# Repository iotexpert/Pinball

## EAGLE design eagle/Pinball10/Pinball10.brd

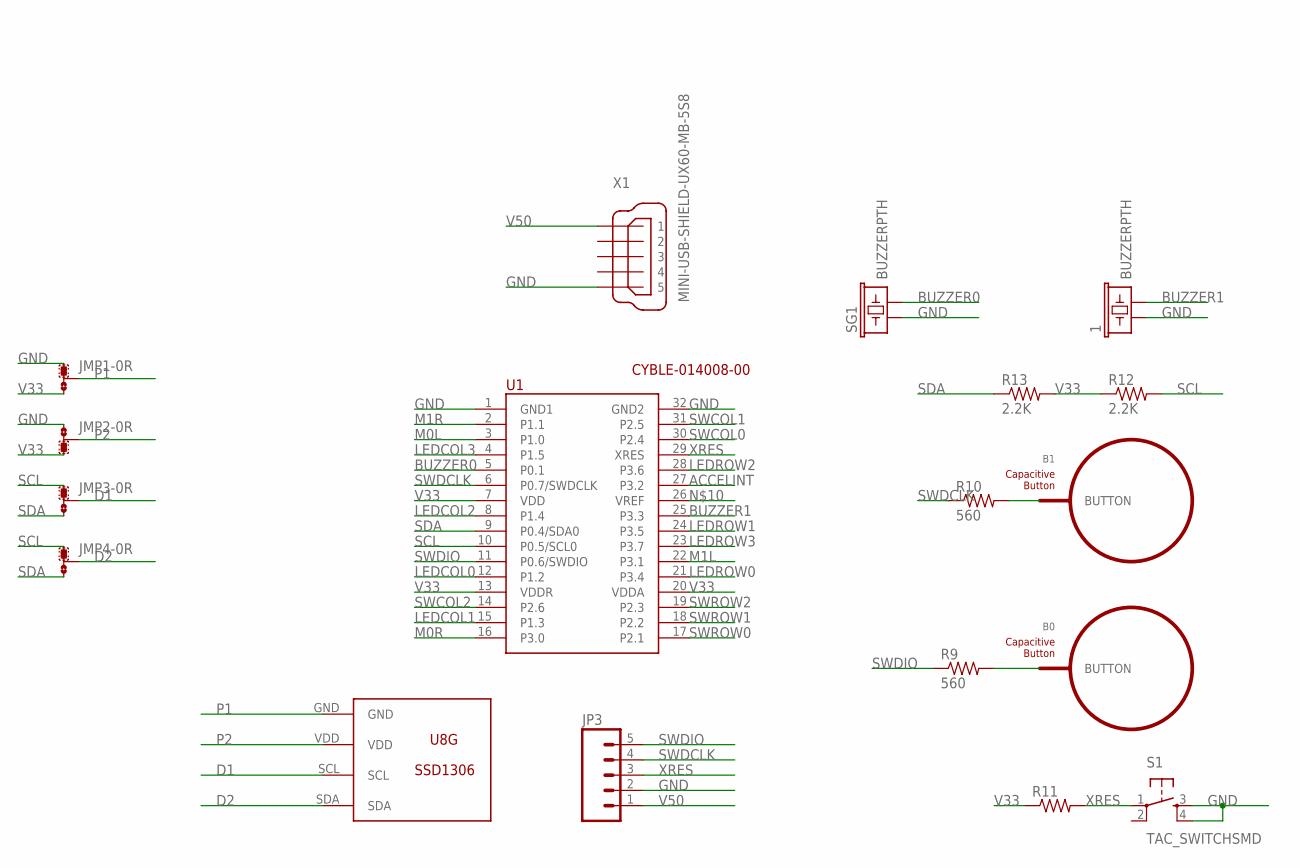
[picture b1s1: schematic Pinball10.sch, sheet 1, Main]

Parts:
1: BUZZERPTH; BUZZER-12MM
B0, B1: BUTTON_PASSIVE12MM; BUTTON_PASSIVE_12MM
JMP1, JMP2, JMP3, JMP4: 0R-JUMPB; B0R-JMP
JP3: M05LOCK; 1X05_LOCK
R9, R10: 560; 0805
R11: RESISTOR0805-RES; 0805
R12, R13: 2.2K; 0805
S1: TAC_SWITCHSMD; TACTILE-SWITCH-SMD
SG1: BUZZERPTH; BUZZER-12MM
U1: CYBLE-014008-00; PSOC-BLE-11MM-32
U$2: U8G-096-OLED; 096-SSD1306
X1: MINI-USB-SHIELD-UX60-MB-5S8; UX60-MB-5S8

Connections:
ACCELINT: U1.27 (P3.2)
BUZZER0: SG1.- (2), U1.5 (P0.1)
BUZZER1: 1.- (2), U1.25 (P3.3)
D1: JMP3.2, U$2.SCL
D2: JMP4.2, U$2.SDA
GND: 1.+ (1), JMP1.1, JMP2.1, JP3.2, S1.3, S1.4, SG1.+ (1), U1.1 (GND1), U1.32 (GND2), X1.5; also elsewhere on the board
LEDCOL0: U1.12 (P1.2); also elsewhere on the board
LEDCOL1: U1.15 (P1.3); also elsewhere on the board
LEDCOL2: U1.8 (P1.4); also elsewhere on the board
LEDCOL3: U1.4 (P1.5); also elsewhere on the board
LEDROW0: U1.21 (P3.4); also elsewhere on the board
LEDROW1: U1.24 (P3.5); also elsewhere on the board
LEDROW2: U1.28 (P3.6); also elsewhere on the board
LEDROW3: U1.23 (P3.7); also elsewhere on the board
M0L: U1.3 (P1.0); also elsewhere on the board
M0R: U1.16 (P3.0); also elsewhere on the board
M1L: U1.22 (P3.1); also elsewhere on the board
M1R: U1.2 (P1.1); also elsewhere on the board
unnamed: B0.BUTTON, R9.2
unnamed: B1.BUTTON, R10.2
P1: JMP1.2, U$2.GND
P2: JMP2.2, U$2.VDD
SCL: JMP3.1, JMP4.1, R12.2, U1.10 (P0.5/SCL0); also elsewhere on the board
SDA: JMP3.3, JMP4.3, R13.1, U1.9 (P0.4/SDA0); also elsewhere on the board
SWCOL0: U1.30 (P2.4); also elsewhere on the board
SWCOL1: U1.31 (P2.5); also elsewhere on the board
SWCOL2: U1.14 (P2.6); also elsewhere on the board
SWDCLK: JP3.4, R10.1, U1.6 (P0.7/SWDCLK)
SWDIO: JP3.5, R9.1, U1.11 (P0.6/SWDIO)
SWROW0: U1.17 (P2.1); also elsewhere on the board
SWROW1: U1.18 (P2.2); also elsewhere on the board
SWROW2: U1.19 (P2.3); also elsewhere on the board
V33: JMP1.3, JMP2.3, R11.1, R12.1, R13.2, U1.7 (VDD), U1.13 (VDDR), U1.20 (VDDA); also elsewhere on the board
V50: JP3.1, X1.1; also elsewhere on the board
XRES: JP3.3, R11.2, S1.1, U1.29 (XRES)

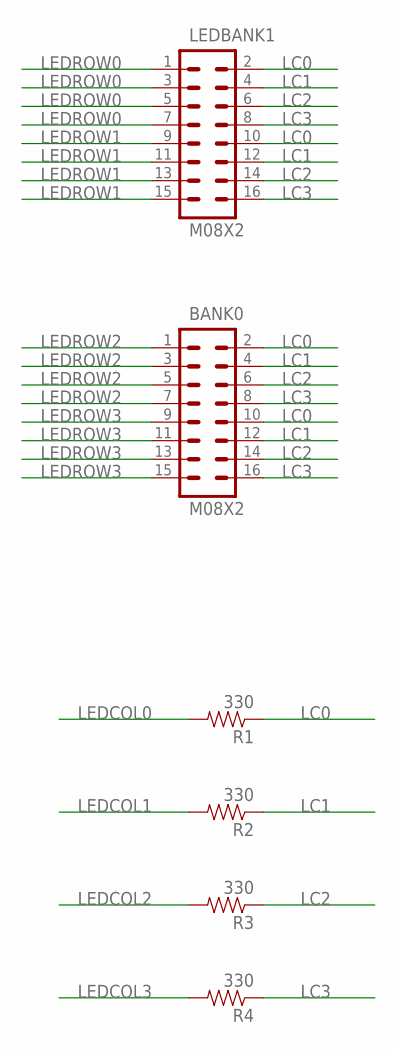
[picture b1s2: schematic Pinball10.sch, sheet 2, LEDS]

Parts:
BANK0: M08X2; 2X8
LEDBANK1: M08X2; 2X8
R1, R2, R3, R4: 330; 0805

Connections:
LC0: BANK0.2, BANK0.10, LEDBANK1.2, LEDBANK1.10, R1.1
LC1: BANK0.4, BANK0.12, LEDBANK1.4, LEDBANK1.12, R2.1
LC2: BANK0.6, BANK0.14, LEDBANK1.6, LEDBANK1.14, R3.1
LC3: BANK0.8, BANK0.16, LEDBANK1.8, LEDBANK1.16, R4.1
LEDCOL0: R1.2; also elsewhere on the board
LEDCOL1: R2.2; also elsewhere on the board
LEDCOL2: R3.2; also elsewhere on the board
LEDCOL3: R4.2; also elsewhere on the board
LEDROW0: LEDBANK1.1, LEDBANK1.3, LEDBANK1.5, LEDBANK1.7; also elsewhere on the board
LEDROW1: LEDBANK1.9, LEDBANK1.11, LEDBANK1.13, LEDBANK1.15; also elsewhere on the board
LEDROW2: BANK0.1, BANK0.3, BANK0.5, BANK0.7; also elsewhere on the board
LEDROW3: BANK0.9, BANK0.11, BANK0.13, BANK0.15; also elsewhere on the board

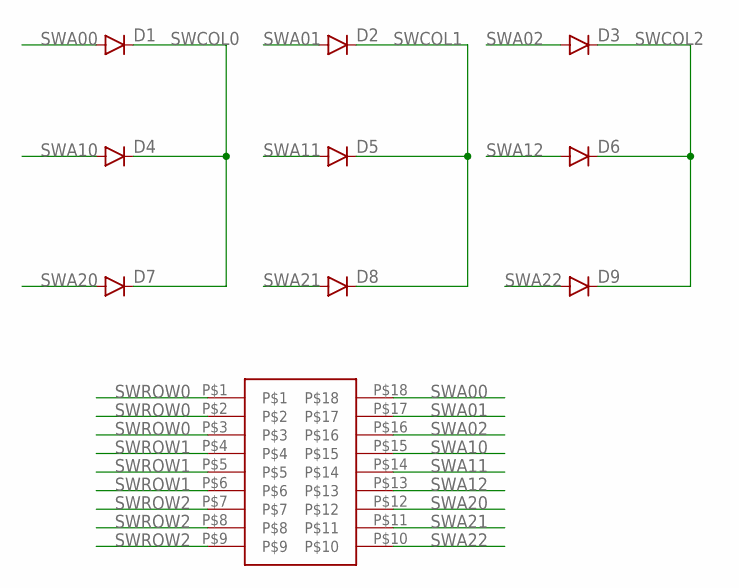
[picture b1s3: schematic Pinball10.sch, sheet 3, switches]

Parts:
D1, D2, D3, D4, D5, D6, D7, D8, D9: DIODESOD; SOD-323
U$1: 9X2

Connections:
SWA00: D1.A, U$1.P$18
SWA01: D2.A, U$1.P$17
SWA02: D3.A, U$1.P$16
SWA10: D4.A, U$1.P$15
SWA11: D5.A, U$1.P$14
SWA12: D6.A, U$1.P$13
SWA20: D7.A, U$1.P$12
SWA21: D8.A, U$1.P$11
SWA22: D9.A, U$1.P$10
SWCOL0: D1.C, D4.C, D7.C; also elsewhere on the board
SWCOL1: D2.C, D5.C, D8.C; also elsewhere on the board
SWCOL2: D3.C, D6.C, D9.C; also elsewhere on the board
SWROW0: U$1.P$1, U$1.P$2, U$1.P$3; also elsewhere on the board
SWROW1: U$1.P$4, U$1.P$5, U$1.P$6; also elsewhere on the board
SWROW2: U$1.P$7, U$1.P$8, U$1.P$9; also elsewhere on the board

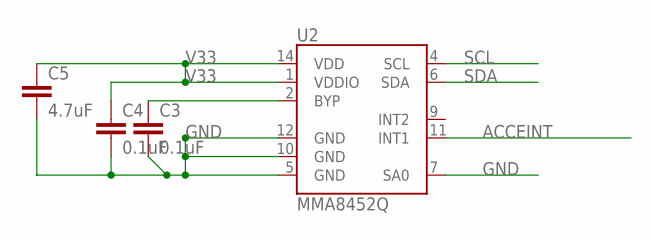
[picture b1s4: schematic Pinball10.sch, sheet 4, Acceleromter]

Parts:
C3, C4: 0.1uF; 0805
C5: 4.7uF; 0805
U2: MMA8452Q; QFN-16_0.5MM

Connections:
ACCEINT: U2.11 (INT1)
GND: C3.2, C4.2, C5.2, U2.5 (GND), U2.7 (SA0), U2.10 (GND), U2.12 (GND); also elsewhere on the board
unnamed: C3.1, U2.2 (BYP)
SCL: U2.4 (SCL); also elsewhere on the board
SDA: U2.6 (SDA); also elsewhere on the board
V33: C4.1, C5.1, U2.1 (VDDIO), U2.14 (VDD); also elsewhere on the board

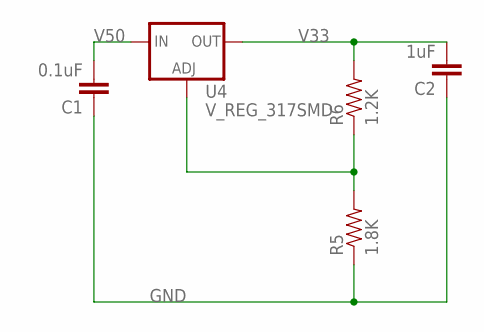
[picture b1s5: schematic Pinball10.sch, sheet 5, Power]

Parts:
C1: 0.1uF; 0805
C2: 1uF; 0805
R5: 1.8K; 0805
R6: 1.2K; 0805
U4: V_REG_317SMD; SOT223

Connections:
GND: C1.1, C2.1, R5.1; also elsewhere on the board
unnamed: R5.2, R6.1, U4.1 (ADJ)
V33: C2.2, R6.2, U4.2 (OUT); also elsewhere on the board
V50: C1.2, U4.3 (IN); also elsewhere on the board

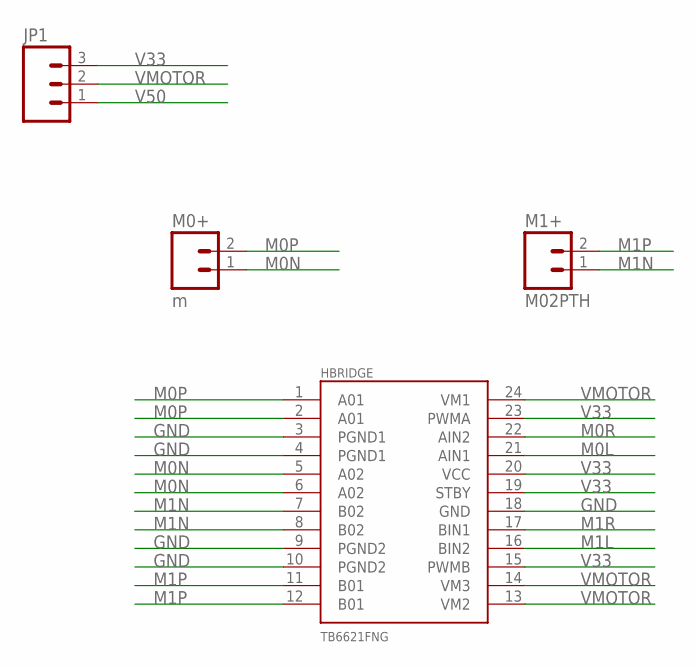
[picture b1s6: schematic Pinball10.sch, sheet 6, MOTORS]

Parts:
HBRIDGE: TB6621FNG; SSOP24
JP1: M03PTH; 1X03
M0+: m; 1X02
M1+: M02PTH; 1X02

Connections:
GND: HBRIDGE.3 (PGND1), HBRIDGE.4 (PGND1), HBRIDGE.9 (PGND2), HBRIDGE.10 (PGND2), HBRIDGE.18 (GND); also elsewhere on the board
M0L: HBRIDGE.21 (AIN1); also elsewhere on the board
M0N: HBRIDGE.5 (A02), HBRIDGE.6 (A02), M0+.1
M0P: HBRIDGE.1 (A01), HBRIDGE.2 (A01), M0+.2
M0R: HBRIDGE.22 (AIN2); also elsewhere on the board
M1L: HBRIDGE.16 (BIN2); also elsewhere on the board
M1N: HBRIDGE.7 (B02), HBRIDGE.8 (B02), M1+.1
M1P: HBRIDGE.11 (B01), HBRIDGE.12 (B01), M1+.2
M1R: HBRIDGE.17 (BIN1); also elsewhere on the board
V33: HBRIDGE.15 (PWMB), HBRIDGE.19 (STBY), HBRIDGE.20 (VCC), HBRIDGE.23 (PWMA), JP1.3; also elsewhere on the board
V50: JP1.1; also elsewhere on the board
VMOTOR: HBRIDGE.13 (VM2), HBRIDGE.14 (VM3), HBRIDGE.24 (VM1), JP1.2

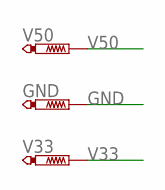
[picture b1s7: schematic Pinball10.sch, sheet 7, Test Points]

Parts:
GND: GND; P1-13
V33, V50: PTR1PAD1-13; P1-13

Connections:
GND: GND.TP; also elsewhere on the board
V33: V33.TP; also elsewhere on the board
V50: V50.TP; also elsewhere on the board

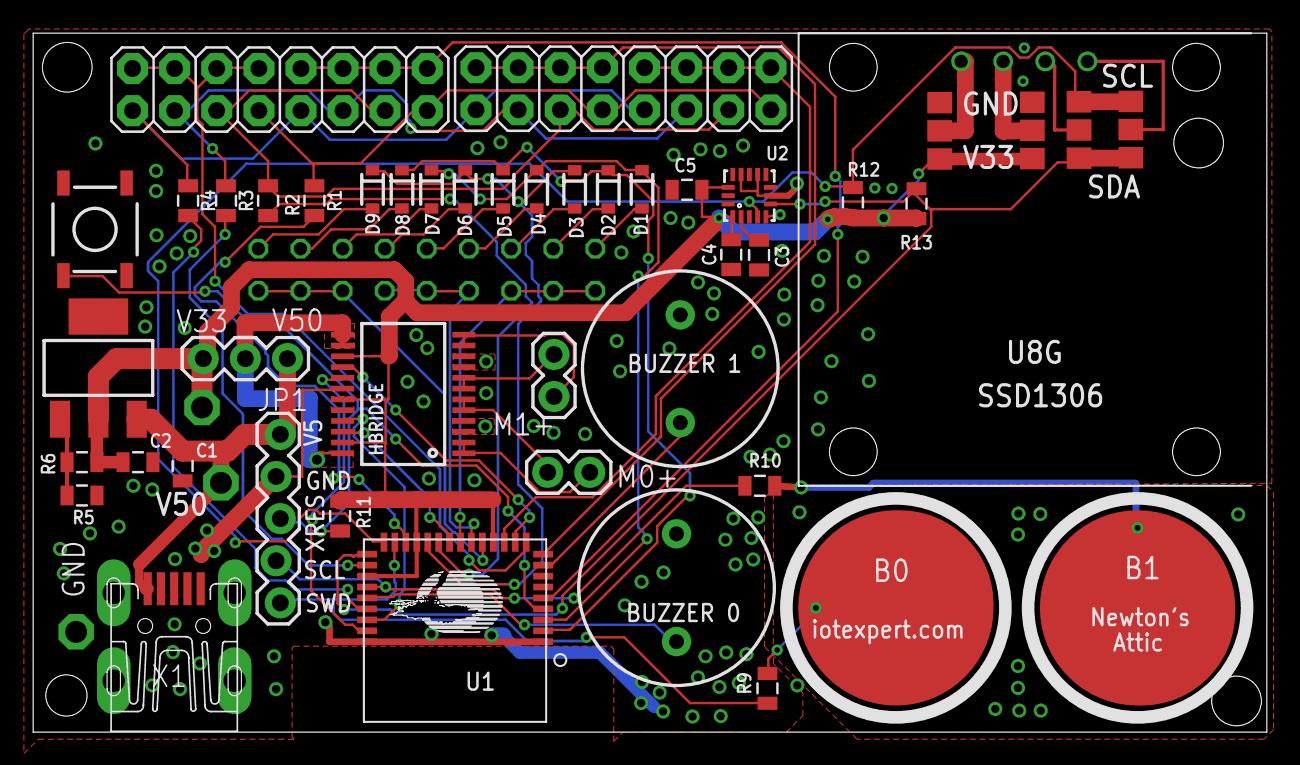
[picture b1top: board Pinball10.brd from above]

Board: 2 copper layers, 74.4 x 42.2 mm, 50 parts (0 on the bottom side), 54 nets.

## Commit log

2016-08-07 intermediate point for LED
2016-08-08 adding test projects
2016-08-08 updated bom
2016-08-11 incremental updates
2016-08-12 Updated bom file
2016-08-13 Last commit before the building the library
2016-08-15 A bunch of changes and new projects
2016-08-20 updates to WIP
2016-08-22 Intermediate progress on switches
2016-08-23 back and forth
2016-08-24 finished component for switch matrix
2016-08-27 board0.9
2016-08-27 labeling done
2016-08-27 maybe 1.0 board?
2016-08-27 fixed errors from ERC (and found a real layout error
2016-08-28 final 1.0c board
2016-08-28 Pinball Wizard 1.0 --- the one I sent to OSHPark
2016-08-28 added some values to the schematic as I filled in the BOM
2016-08-29 updates to the bom
2016-09-06 updates to excel sheets with schedule and bom
2016-09-06 intermediate version of music
2016-09-07 Fixed music firmware... version 0.9
2016-09-08 updates to music
2016-09-09 First instance of the Music Player
2016-09-14 music player updates
2016-09-21 Fixed MusicPlayer Component firmware
2016-11-18 the board ... but with the crash
2016-11-18 completed 1.1 of board
2016-12-19 New layout
2016-12-22 Released version 1.2 of board
2017-01-02 a bunch of changes to the test firmware

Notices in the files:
parts and their libraries:
PatternAgents-Cypress: License : http://creativecommons.org/licenses/by-sa/3.0
(Creative Commons 3.0)
SparkFun-Connectors: Licensing: Creative Commons ShareAlike 4.0 International - https://creativecommons.org/licenses/by-sa/4.0
